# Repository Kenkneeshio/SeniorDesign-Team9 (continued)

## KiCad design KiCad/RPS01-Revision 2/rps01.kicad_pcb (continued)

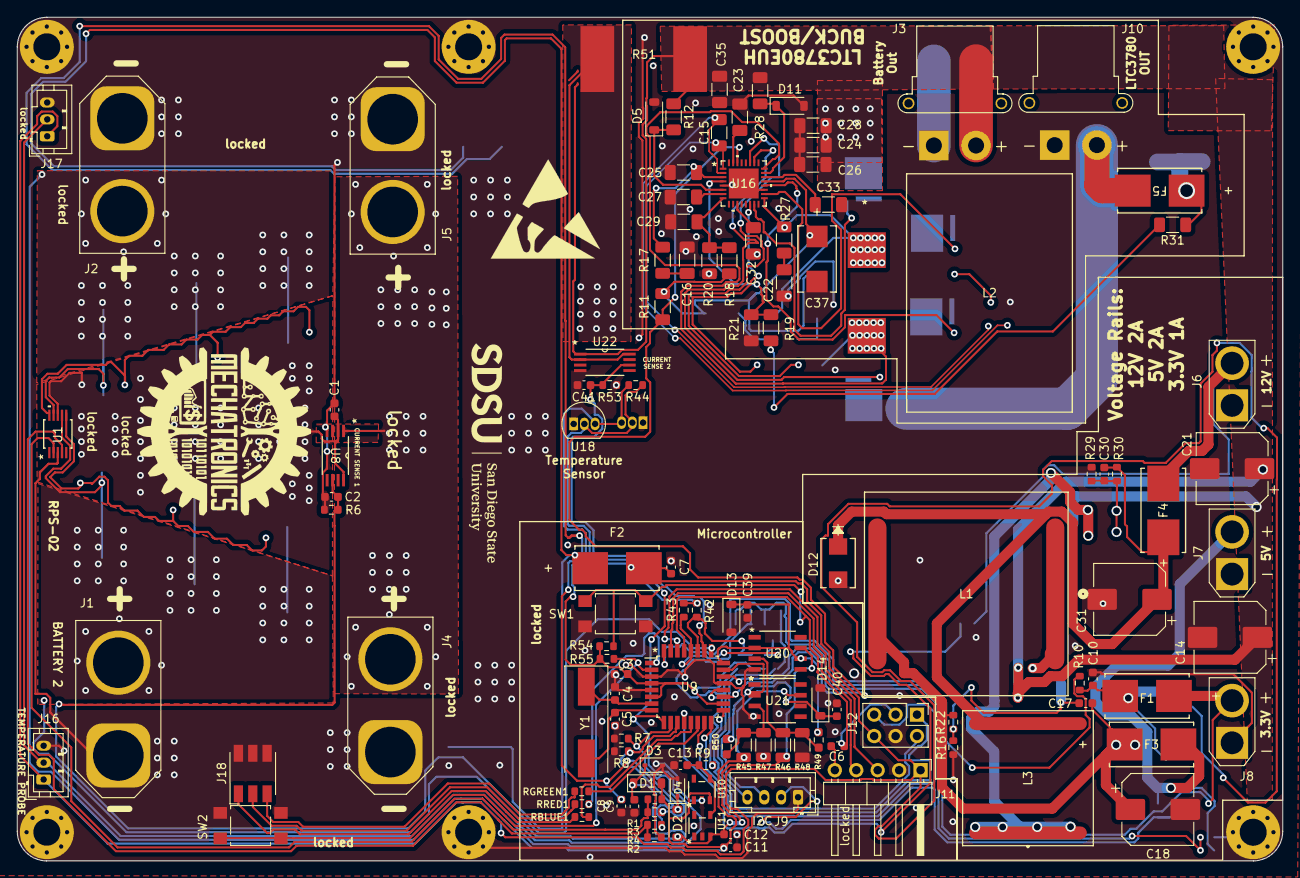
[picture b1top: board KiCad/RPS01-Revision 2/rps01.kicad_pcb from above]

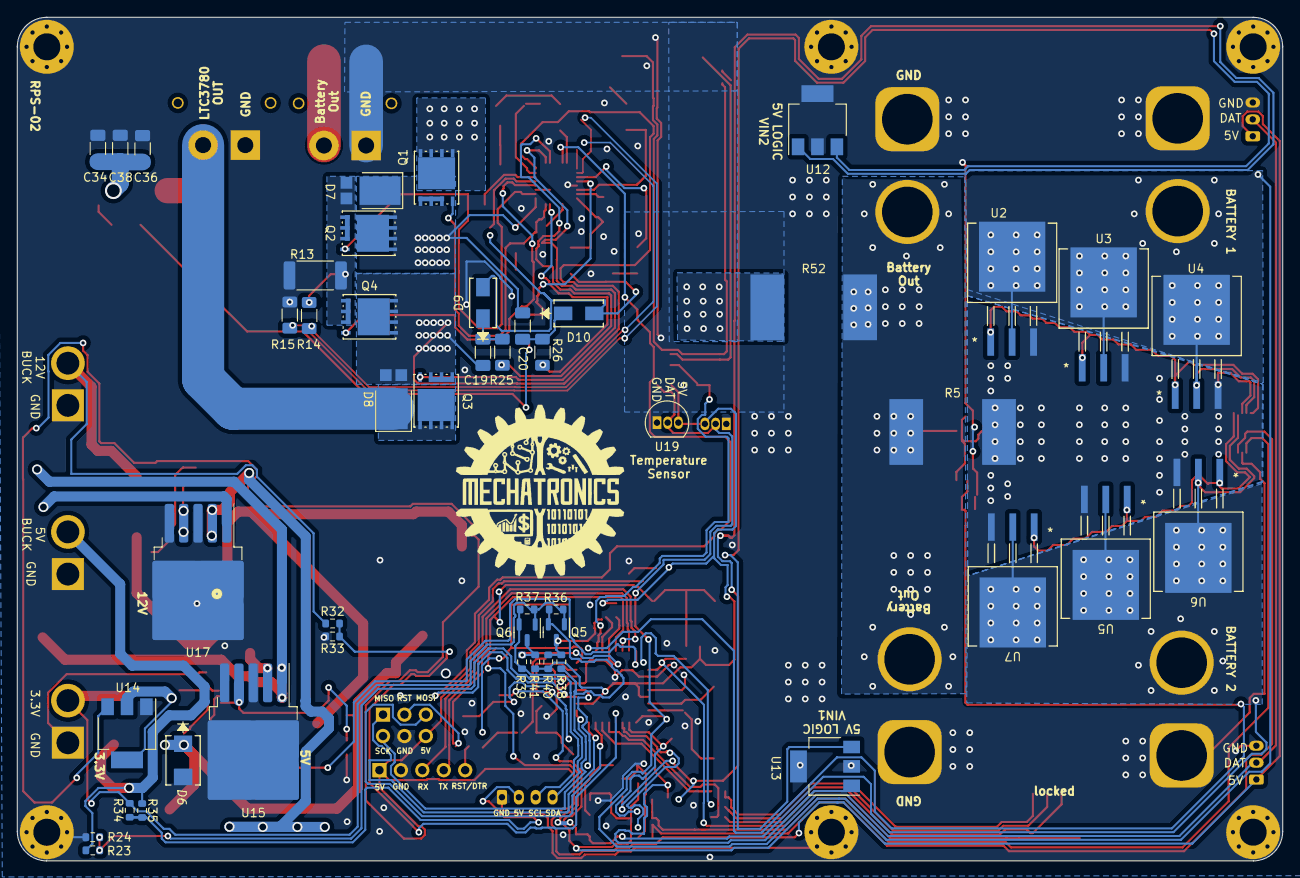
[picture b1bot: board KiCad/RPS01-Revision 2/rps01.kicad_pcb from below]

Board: 2 copper layers, 150.0 x 100.0 mm, 173 parts (47 on the bottom side), 88 nets.

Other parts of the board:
C11, C12, C13: 0.1u; C_0603_1608Metric
R9, R10: 0; R_0603_1608Metric
R51: 3m; CSS2H-5930R
R52: 0; CSS2H-5930R
U10, U11: ADR02AUJZ-REEL7; ADR02AUJZ_REEL7_UJ_5_ADI

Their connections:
+BATT: R51.1, R52.1, R52.2; also elsewhere on the board
+BATT2: R51.2; also elsewhere on the board
AREF: R9.2; also elsewhere on the board
unnamed: C13.1, R9.1, U10.4 (VOUT), U11.4 (VOUT)
PD2: R10.1; also elsewhere on the board

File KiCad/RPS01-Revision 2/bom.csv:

Designator,Footprint,Quantity,Value,LCSC Part #,MFR Part #,Description
"C1, C2, C11, C12, C13, C3, C39, C40, C41",603,9,0.1u,C91183,CC0603JRX7R9BB104,50V 100nF X7R ±5% 0603 Multilayer Ceramic Capacitors MLCC - SMD/SMT ROHS
C10,603,1,22u,C159801,CL10A226MQ8NRNE,6.3V 22uF X5R ±20% 0603 Multilayer Ceramic Capacitors MLCC - SMD/SMT ROHS
C15,1206,1,68p,C440203,GRM31A5C3A680JW01D,1kV 68pF null ±5% 1206 Multilayer Ceramic Capacitors MLCC - SMD/SMT ROHS
C16,1206,1,3.3n,C2847434,FN31N332J500PXG,50V 3.3nF C0G ±5% 1206 Multilayer Ceramic Capacitors MLCC - SMD/SMT ROHS
"C18, C31",CP_Elec_8x10,2,220u,C3008507,EMZA350ARA221MHA0G,"220uF 35V 300mA@120Hz ±20% SMD,D8xL10mm Aluminum Electrolytic Capacitors - SMD ROHS"
C22,1206,1,1n,C541590,CC1206FRNPO9BN102,50V 1nF NP0 ±1% 1206 Multilayer Ceramic Capacitors MLCC - SMD/SMT ROHS
C23,1206,1,.22u,C464977,GRM31C5C1H224JE02L,50V 220nF C0G ±5% 1206 Multilayer Ceramic Capacitors MLCC - SMD/SMT ROHS
"C24, C26, C28",1206,3,10u 35V,C412612,GMJ316BB7106KLHT,35V 10uF X7R ±10% 1206 Multilayer Ceramic Capacitors MLCC - SMD/SMT ROHS
C25,1206,1,47p,C1916,1206CG470J500NT,50V 47pF C0G ±5% 1206 Multilayer Ceramic Capacitors MLCC - SMD/SMT ROHS
C27,1206,1,1000p,C717608,TCC1206X7R102K202FT,2kV 1000pF X7R ±10% 1206 Multilayer Ceramic Capacitors MLCC - SMD/SMT ROHS
C29,1206,1,10000p,C55077,1206B103K101NT,100V 10nF X7R ±10% 1206 Multilayer Ceramic Capacitors MLCC - SMD/SMT ROHS
C32,1206,1,0.01u,C296117,1206N103G500CT,50V 10nF NP0 ±2% 1206 Multilayer Ceramic Capacitors MLCC - SMD/SMT ROHS
C33,1206,1,1u,C85867,GCM31MR71H105KA55L,50V 1uF X7R ±10% 1206 Multilayer Ceramic Capacitors MLCC - SMD/SMT ROHS
"C34, C36, C38",1206,3,22u 16V,C412630,LMK316ABJ226KL-T,10V 22uF X5R ±10% 1206 Multilayer Ceramic Capacitors MLCC - SMD/SMT ROHS
C35,1206,1,0.1u,C97946,GRM31C5C1H104JA01L,50V 100nF C0G ±5% 1206 Multilayer Ceramic Capacitors MLCC - SMD/SMT ROHS
"C4, C5",603,2,22p,C296053,0603N220F101CT,100V 22pF NP0 ±1% 0603 Multilayer Ceramic Capacitors MLCC - SMD/SMT ROHS
C6,603,1,100n,C128615,0603B103J500CT,50V 10nF X7R ±5% 0603 Multilayer Ceramic Capacitors MLCC - SMD/SMT ROHS
"C8, C9",603,2,0.22u,C726561,AC0603KRX7R8BB224,25V 220nF X7R ±10% 0603 Multilayer Ceramic Capacitors MLCC - SMD/SMT ROHS
"D1, D2",D_SOD-123,2,B0540W-7-F,C154764,B0540W-7-F,40V 510mV@500mA 500mA SOD-123 Schottky Barrier Diodes (SBD) ROHS
"D10, D9",SMC(DO-214AB),2,B0540W,C110486,B340-13-F,40V 500mV@3A 3A SMC(DO-214AB) Schottky Barrier Diodes (SBD) ROHS
D11,SOD-123,1,36V Zener,C444414,DDZ36-7,±2.5% Single 35.36V~37.19V 310mW 36V SOD-123 Zener Diodes ROHS
"D12, D6",DO-214AA,2,SSB43L-E3/52T,C5338051,DO-214AA,40V 0.45V 5A DO-214AA Schottky Barrier Diodes (SBD) ROHS
"D13, D14",SOD-123,2,MMSZ5247BT1G,C236089,MMSZ5247BT1G,±5% Single 16.15V~17.85V 500mW 17V SOD-123 Zener Diodes ROHS
"D3, D4",SOD-323,2,MM3Z5V1ST1G,"C236206",MM3Z5V1ST1G,±2% Single 4.98V~5.2V 300mW 5.1V SOD-323 Zener Diodes ROHS
"Q5, Q6",SOT-23(TO-236),2,BSS138,C358381,BSS138,"50V 220mA 3.5Ω@10V,220mA 360mW N Channel SOT-23(TO-236) MOSFETs ROHS"
"R1, R2, R35, R38, R39, R49, R50, R9",603,8,0,C269698,RMC060301%N,100mW 1% 0Ω 0603 Chip Resistor - Surface Mount ROHS
R10,603,1,0,C269698,RMC060301%N,100mW 1% 0Ω 0603 Chip Resistor - Surface Mount ROHS
R11,1206,1,10k,C104595,RTT061002FTP,250mW ±100ppm/℃ ±1% 10kΩ 1206 Chip Resistor - Surface Mount ROHS
R12,1206,1,51K,C319552,AR06DTDV5102,250mW Thin Film Resistor ±0.5% ±50ppm/℃ 51kΩ 1206 Chip Resistor - Surface Mount ROHS
R13,2512,1,25m 1%,C2903480,HoJLR2512-3W-25mR-1%,3W 25mΩ 2512 Current Sense Resistors/Shunt Resistors ROHS
"R14, R15",1206,2,100 1%,C409744,AR06FTCV1000,250mW Thin Film Resistor ±25ppm/℃ ±1% 100Ω 1206 Chip Resistor - Surface Mount ROHS
"R16, R29",603,2,1k,C100050,"RC0603DR-071KL",100mW Thick Film Resistors ±100ppm/℃ ±0.5% 1kΩ 0603 Chip Resistor - Surface Mount ROHS
R17,1206,1,30K,C171081,WR12X3002FTL,250mW Thick Film Resistors ±100ppm/℃ ±1% 30kΩ 1206 Chip Resistor - Surface Mount ROHS
R18,1206,1,47.5K 1%,C319618,AR06BTDV4752,250mW Thin Film Resistor ±50ppm/℃ ±0.1% 47.5kΩ 1206 Chip Resistor - Surface Mount ROHS
R20,1206,1,12.4K 1%,C139133,1206W4F1242T5E,250mW Thick Film Resistors ±100ppm/℃ ±1% 12.4kΩ 1206 Chip Resistor - Surface Mount ROHS
R21,1206,1,8.06K 1%,C323152,RS-06K8061FT,250mW ±100ppm/℃ ±1% 8.06kΩ 1206 Chip Resistor - Surface Mount ROHS
"R25, R26",1206,2,0,C2907363,FRC1206F0000TS,250mW Thick Film Resistors ±1% 0Ω 1206 Chip Resistor - Surface Mount ROHS
R27,1206,1,1,C2960691,FRC1206F1R05TS,250mW Thick Film Resistors ±1% ±200ppm/℃ 1.05Ω 1206 Chip Resistor - Surface Mount ROHS
"R28, R31",1206,2,10,C2933578,FRC1206F10R5TS,250mW Thick Film Resistors ±100ppm/℃ ±1% 10.5Ω 1206 Chip Resistor - Surface Mount ROHS
R30,603,1,"8.87k
",C2998144,FRC0603F8871TS,100mW Thick Film Resistors ±100ppm/℃ ±1% 8.87kΩ 0603 Chip Resistor - Surface Mount ROHS
"R36, R37, R40, R41",603,4,10K,C191124,ERJ3EKF1002V,100mW Thick Film Resistors ±100ppm/℃ ±1% 10000Ω 0603 Chip Resistor - Surface Mount ROHS
"R42, R43, R44, R54, R55, R7, R8",603,7,4.7K,C103656,RTT034701FTP,100mW Thick Film Resistors ±100ppm/℃ ±1% 4.7kΩ 0603 Chip Resistor - Surface Mount ROHS
"R45, R46",1206,2,1.2M,C323198,RS-06L1204FT,250mW ±1% ±250ppm/℃ 1.2MΩ 1206 Chip Resistor - Surface Mount ROHS
"R47, R48",1206,2,510K,C2114457,AA1206FR-07510KL,250mW Thick Film Resistors ±1% ±150ppm/℃ 510kΩ 1206 Chip Resistor - Surface Mount ROHS
R6,603,1,150k,C319876,AR03BTCX1503,100mW Thin Film Resistor ±25ppm/℃ ±0.1% 150kΩ 0603 Chip Resistor - Surface Mount ROHS
RBLUE1,603,1,150 Blue,C3017754,SCR0603J150R,±5% 150Ω 0603 Chip Resistor - Surface Mount ROHS
RGREEN1,603,1,150 Green,C3017754,SCR0603J150R,±5% 150Ω 0603 Chip Resistor - Surface Mount ROHS
RRED1,603,1,100 RED,C2906981,FRC0603F1000TS,100mW Thick Film Resistors ±100ppm/℃ ±1% 100Ω 0603 Chip Resistor - Surface Mount ROHS
SW1,SW_SPST_TL3305A,1,RST,C2886899,TL3305AF160QG,NO 50mA 100MΩ 500000 Times 12V 160gf Brick nogging SPST - Tactile Switches ROHS
SW2,SW_SPST_TL3305A,1,Display Button,C2886899,TL3305AF160QG,NO 50mA 100MΩ 500000 Times 12V 160gf Brick nogging SPST - Tactile Switches ROHS
"U10, U11",TSOT-5L,2,ADR02AUJZ-REEL7,C141936,ADR02AUJZ-REEL7,5V ±0.1% 7V~36V 10mA Fixed SOT-23-5 Voltage References ROHS
"U12, U13",SOT-223-4,2,LM340MPX-5.0/NOPB,C2860024,LM340MPX-5.0/NOPB,70dB@(120Hz) 1.5A null 5V positive 35V SOT-223-4 Linear Voltage Regulators (LDO) ROHS
"U20, U21",SOP-8,2,UA741CDT,C7111,UA741CDT,10nA 1 1MHz SOP-8 Operational Amplifier ROHS

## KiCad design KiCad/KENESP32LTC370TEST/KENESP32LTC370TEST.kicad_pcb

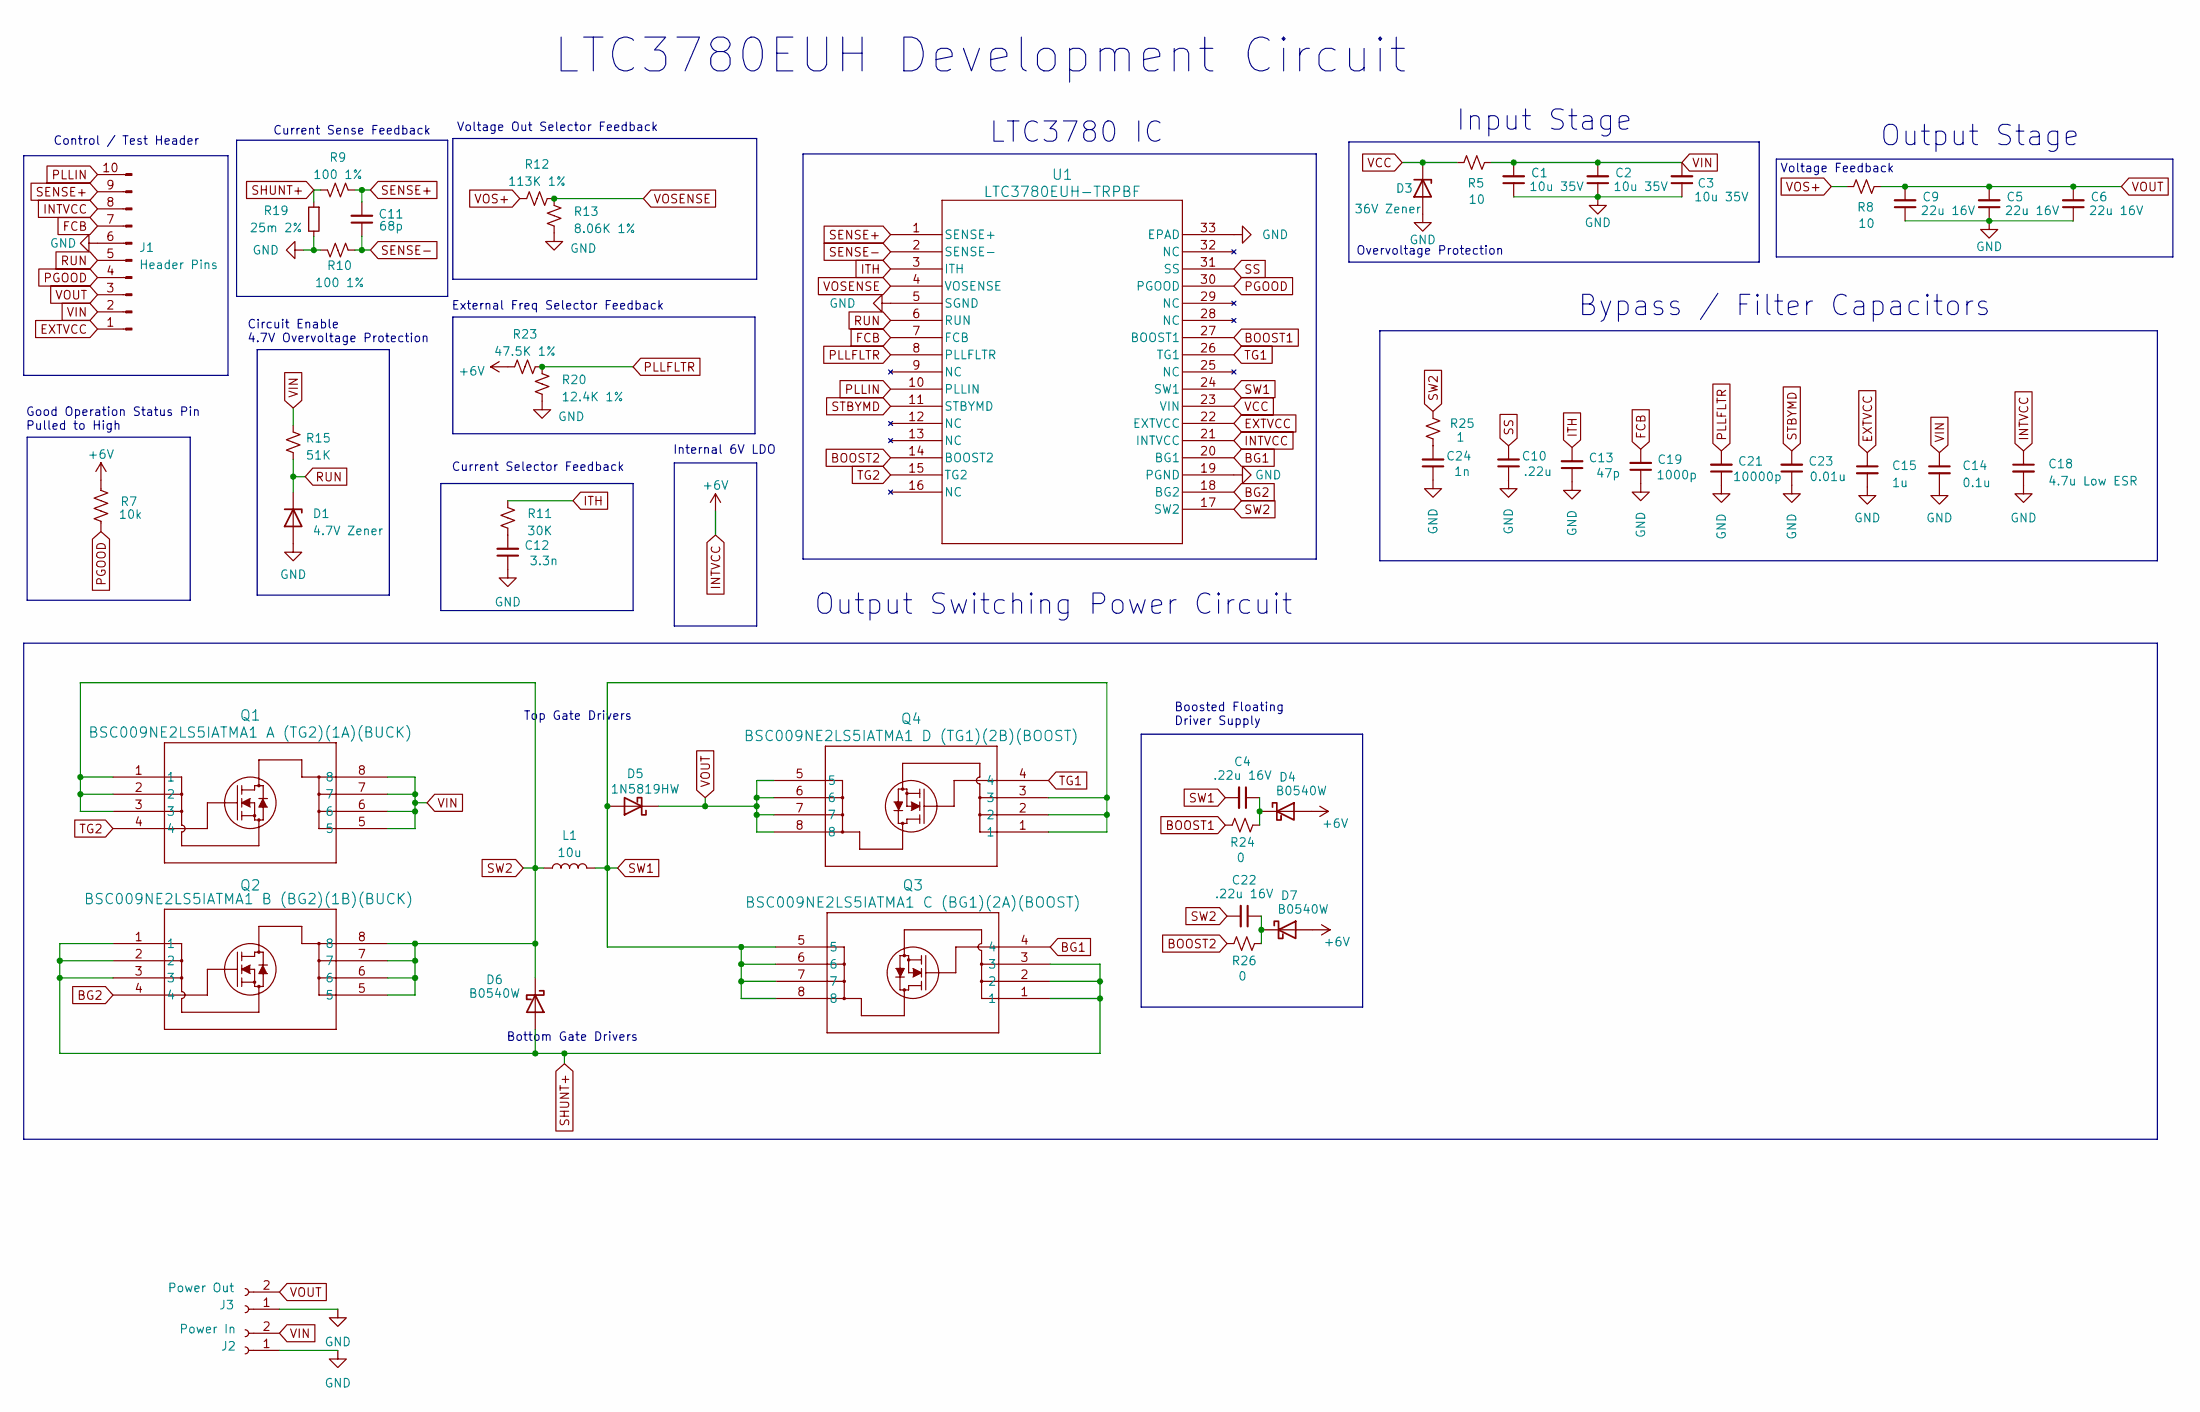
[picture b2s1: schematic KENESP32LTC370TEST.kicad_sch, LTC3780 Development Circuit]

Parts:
C1, C2, C3: 10u 35V; C_1206_3216Metric_Pad1.33x1.80mm_HandSolder
C4, C22: .22u 16V; C_1206_3216Metric_Pad1.33x1.80mm_HandSolder
C5, C6, C9: 22u 16V; C_1206_3216Metric_Pad1.33x1.80mm_HandSolder
C10: .22u; C_1206_3216Metric_Pad1.33x1.80mm_HandSolder
C11: 68p; C_1206_3216Metric_Pad1.33x1.80mm_HandSolder
C12: 3.3n; C_1206_3216Metric_Pad1.33x1.80mm_HandSolder
C13: 47p; C_1206_3216Metric_Pad1.33x1.80mm_HandSolder
C14: 0.1u; C_1206_3216Metric_Pad1.33x1.80mm_HandSolder
C15: 1u; C_1206_3216Metric_Pad1.33x1.80mm_HandSolder
C18: 4.7u Low ESR; LOWESRCAPMP7.6X4.3_3.1N_KEM
C19: 1000p; C_1206_3216Metric_Pad1.33x1.80mm_HandSolder
C21: 10000p; C_1206_3216Metric_Pad1.33x1.80mm_HandSolder
C23: 0.01u; C_1206_3216Metric_Pad1.33x1.80mm_HandSolder
C24: 1n; C_1206_3216Metric_Pad1.33x1.80mm_HandSolder
D1: 4.7V Zener; D_SOD-123
D3: 36V Zener; D_SOD-123
D4, D6, D7: B0540W; CR_SMA_320-340AE_DIO
D5: 1N5819HW; CR_SMA_320-340AE_DIO
J1: Header Pins; PinHeader_1x10_P2.54mm_Vertical
J2: Power In; AMASS_XT30U-M_1x02_P5.0mm_Vertical
J3: Power Out; AMASS_XT30U-F_1x02_P5.0mm_Vertical
L1: 10u; IND_410680_WRE
Q1: BSC009NE2LS5IATMA1 A (TG2)(1A)(BUCK); PG-TDSON-8_INF
Q2: BSC009NE2LS5IATMA1 B (BG2)(1B)(BUCK); PG-TDSON-8_INF
Q3: BSC009NE2LS5IATMA1 C (BG1)(2A)(BOOST); PG-TDSON-8_INF
Q4: BSC009NE2LS5IATMA1 D (TG1)(2B)(BOOST); PG-TDSON-8_INF
R5, R8: 10; R_1206_3216Metric_Pad1.30x1.75mm_HandSolder
R7: 10k; R_1206_3216Metric_Pad1.30x1.75mm_HandSolder
R9, R10: 100 1%; R_1206_3216Metric_Pad1.30x1.75mm_HandSolder
R11: 30K; R_1206_3216Metric_Pad1.30x1.75mm_HandSolder
R12: 113K 1%; R_1206_3216Metric_Pad1.30x1.75mm_HandSolder
R13: 8.06K 1%; R_1206_3216Metric_Pad1.30x1.75mm_HandSolder
R15: 51K; R_1206_3216Metric_Pad1.30x1.75mm_HandSolder
R19: 25m 2%; R_1206_3216Metric_Pad1.30x1.75mm_HandSolder
R20: 12.4K 1%; R_1206_3216Metric_Pad1.30x1.75mm_HandSolder
R23: 47.5K 1%; R_1206_3216Metric_Pad1.30x1.75mm_HandSolder
R24, R26: 0; R_1206_3216Metric_Pad1.30x1.75mm_HandSolder
R25: 1; R_1206_3216Metric_Pad1.30x1.75mm_HandSolder
U1: LTC3780EUH-TRPBF; QFN-32_UH_LIT

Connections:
BG1: Q3.4, U1.20 (BG1)
BG2: Q2.4, U1.18 (BG2)
BOOST1: R24.1, U1.27 (BOOST1)
BOOST2: R26.1, U1.14 (BOOST2)
EXTVCC: C15.1, J1.1, U1.22 (EXTVCC)
FCB: C19.2, J1.7, U1.7 (FCB)
GND: C1.1, C2.1, C3.1, C5.1, C6.1, C9.1, C10.1, C12.1, C13.1, C14.2, C15.2, C18.2, C19.1, C21.1, C23.1, C24.1, D1.2 (A), D3.2 (A), J1.6, J2.1, J3.1, R10.2, R13.2, R19.2, R20.2, U1.5 (SGND), U1.19 (PGND), U1.33 (EPAD)
INTVCC: C18.1, D4.2 (A), D7.2 (A), J1.8, R7.1, R23.1, U1.21 (INTVCC)
ITH: C13.2, R11.1, U1.3 (ITH)
unnamed: C12.2, R11.2
unnamed: C24.2, R25.1
unnamed: C4.1, D4.1 (K), R24.2
unnamed: C22.1, D7.1 (K), R26.2
PGOOD: J1.4, R7.2, U1.30 (PGOOD)
PLLFLTR: C21.2, R20.1, R23.2, U1.8 (PLLFLTR)
PLLIN: J1.10, U1.10 (PLLIN)
RUN: D1.1 (K), J1.5, R15.2, U1.6 (RUN)
SENSE+: C11.2, J1.9, R9.1, U1.1 (SENSE+)
SENSE-: C11.1, R10.1, U1.2 (SENSE-)
SHUNT+: D6.2 (A), Q2.1, Q2.2, Q2.3, Q3.1, Q3.2, Q3.3, R9.2, R19.1
SS: C10.2, U1.31 (SS)
STBYMD: C23.2, U1.11 (STBYMD)
SW1: C4.2, D5.2 (A), L1.2, Q3.5, Q3.6, Q3.7, Q3.8, Q4.1, Q4.2, Q4.3, U1.24 (SW1)
SW2: C22.2, D6.1 (K), L1.1, Q1.1, Q1.2, Q1.3, Q2.5, Q2.6, Q2.7, Q2.8, R25.2, U1.17 (SW2)
TG1: Q4.4, U1.26 (TG1)
TG2: Q1.4, U1.15 (TG2)
VCC: D3.1 (K), R5.2, U1.23 (VIN)
VIN: C1.2, C2.2, C3.2, C14.1, J1.2, J2.2, Q1.5, Q1.6, Q1.7, Q1.8, R5.1, R15.1
VOS+: R8.2, R12.1
VOSENSE: R12.2, R13.1, U1.4 (VOSENSE)
VOUT: C5.2, C6.2, C9.2, D5.1 (K), J1.3, J3.2, Q4.5, Q4.6, Q4.7, Q4.8, R8.1

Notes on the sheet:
Control / Test Header
Boosted Floating Driver Supply
LTC3780 IC
Input Stage
Voltage Out Selector Feedback
Top Gate Drivers
LTC3780EUH Development Circuit
Bypass / Filter Capacitors
External Freq Selector Feedback
Good Operation Status Pin Pulled to High
Overvoltage Protection
Internal 6V LDO
Circuit Enable 4.7V Overvoltage Protection
Voltage Feedback
Current Selector Feedback
Output Switching Power Circuit
Bottom Gate Drivers
Current Sense Feedback
Output Stage

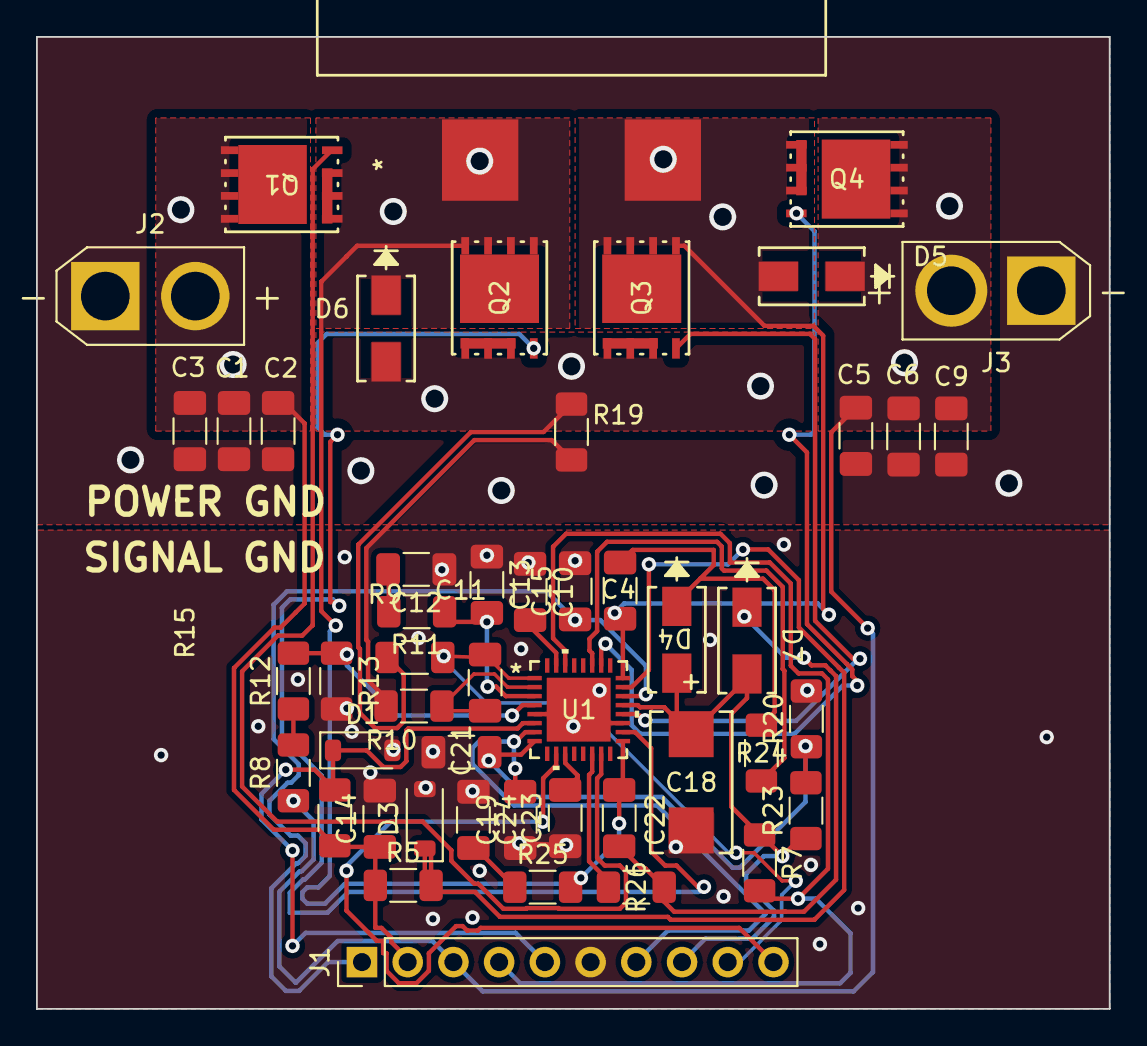
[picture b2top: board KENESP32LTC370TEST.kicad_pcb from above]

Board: 2 copper layers, 59.6 x 54.0 mm, 49 parts (0 on the bottom side), 31 nets.

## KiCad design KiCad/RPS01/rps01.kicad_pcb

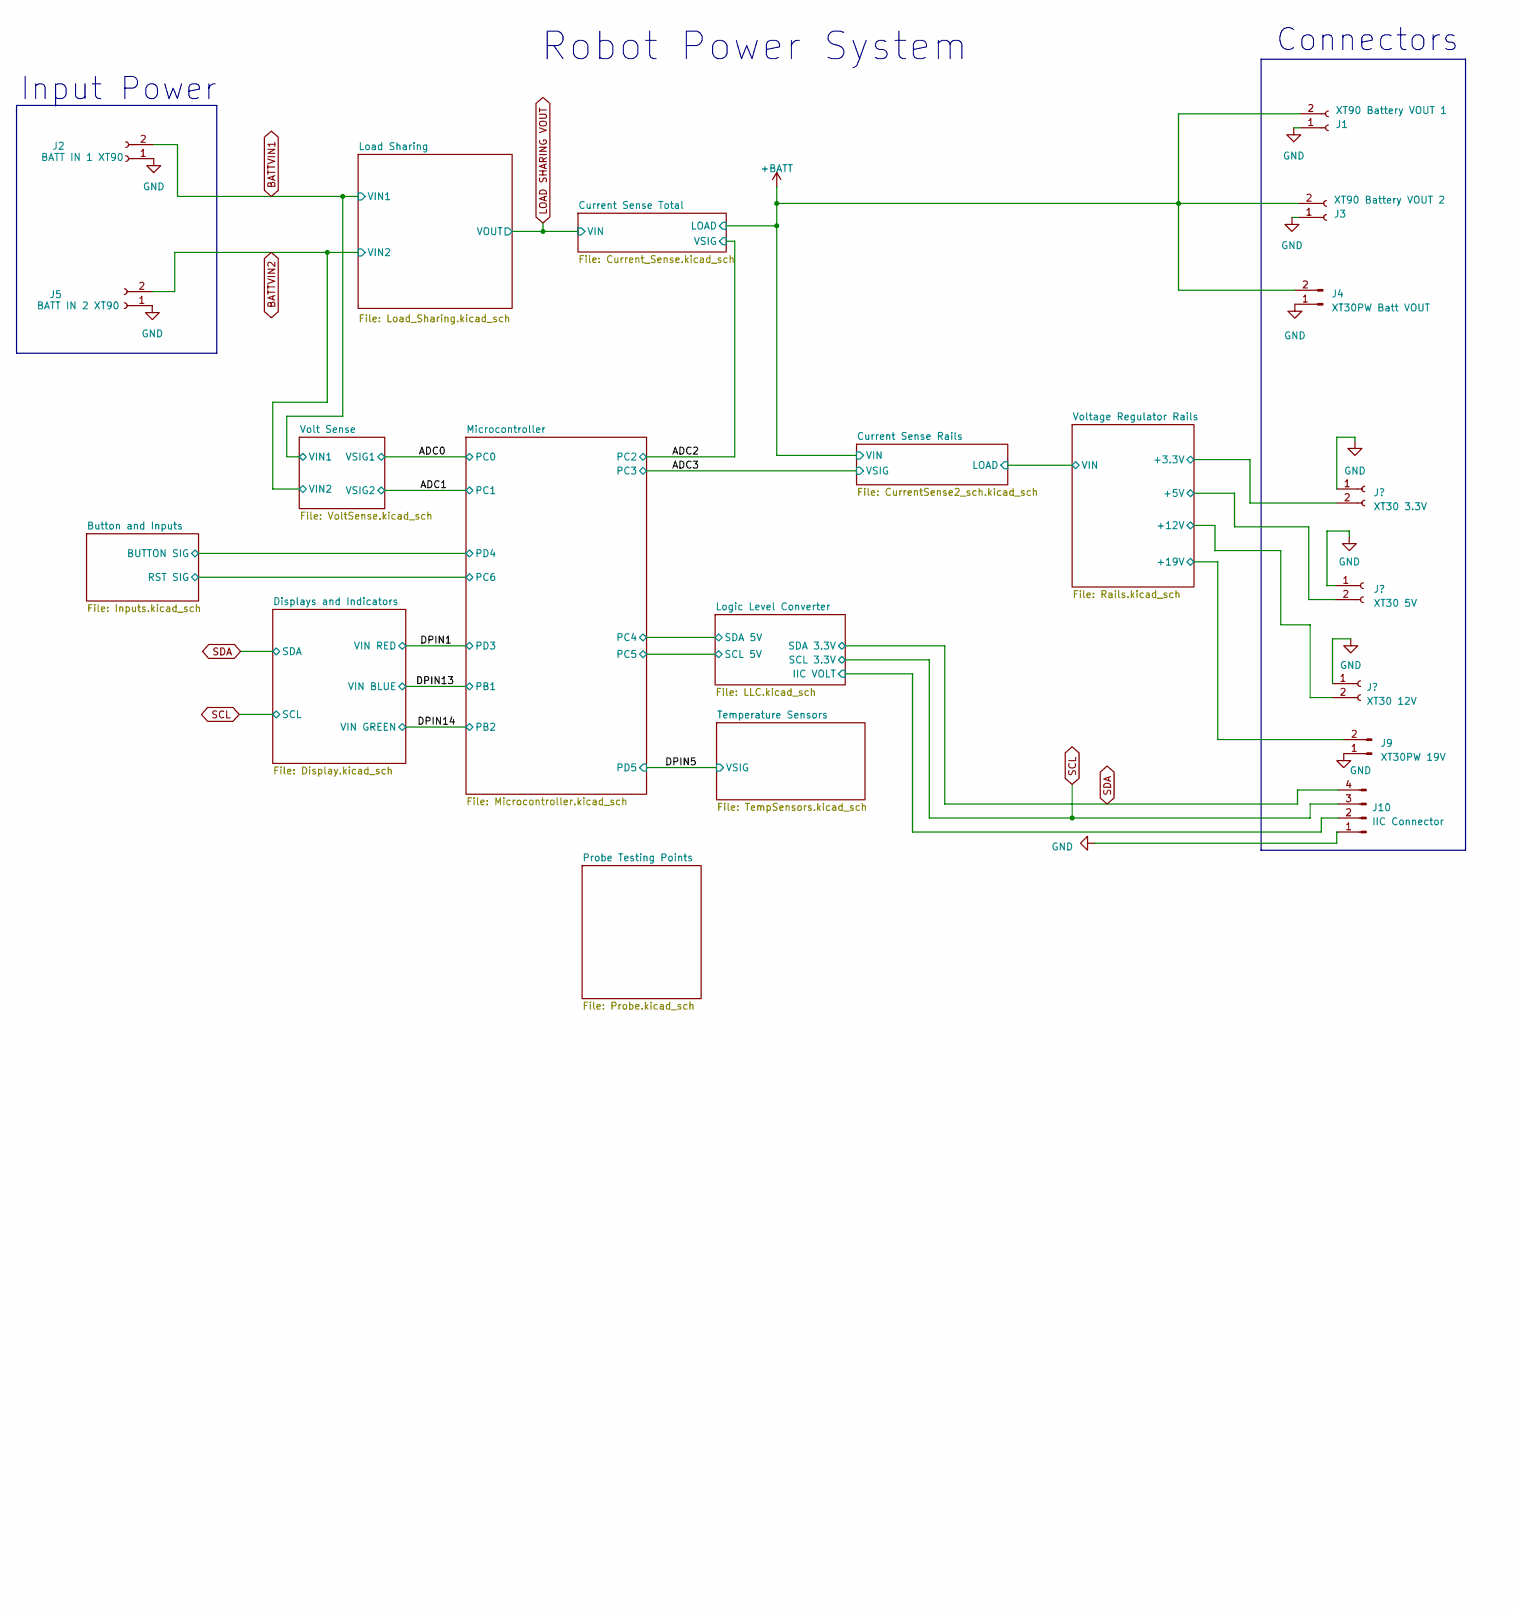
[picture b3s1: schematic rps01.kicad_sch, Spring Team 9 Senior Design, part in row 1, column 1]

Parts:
J1: XT90 Battery VOUT 1; AMASS_XT90-F_1x02_P11.00mm_Vertical
J2: BATT IN 1 XT90; AMASS_XT90-M_1x02_P11.00mm_Vertical
J3: XT90 Battery VOUT 2; AMASS_XT90-F_1x02_P11.00mm_Vertical
J4: XT30PW Batt VOUT; AMASS_XT30PW-F_1x02_P2.50mm_Horizontal
J5: BATT IN 2 XT90; AMASS_XT90-M_1x02_P11.00mm_Vertical
J6: XT30 3.3V; AMASS_XT30U-F_1x02_P5.0mm_Vertical
J7: XT30 5V; AMASS_XT30U-F_1x02_P5.0mm_Vertical
J8: XT30 12V; AMASS_XT30U-F_1x02_P5.0mm_Vertical
J9: XT30PW 19V; AMASS_XT30PW-F_1x02_P2.50mm_Horizontal
J10: IIC Connector; JST_PH_B4B-PH-K_1x04_P2.00mm_Vertical

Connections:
+3.3V: J6.2; also elsewhere on the board
+5V: J7.2; also elsewhere on the board
+12V: J8.2; also elsewhere on the board
+19V: J9.2; also elsewhere on the board
/Logic Level Converter/IIC VOLT: J10.2; also elsewhere on the board
BATTVIN1: J2.2; also elsewhere on the board
BATTVIN2: J5.2; also elsewhere on the board
SCL: J10.3; also elsewhere on the board
SDA: J10.4; also elsewhere on the board

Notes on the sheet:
Connectors
Robot Power System
Input Power

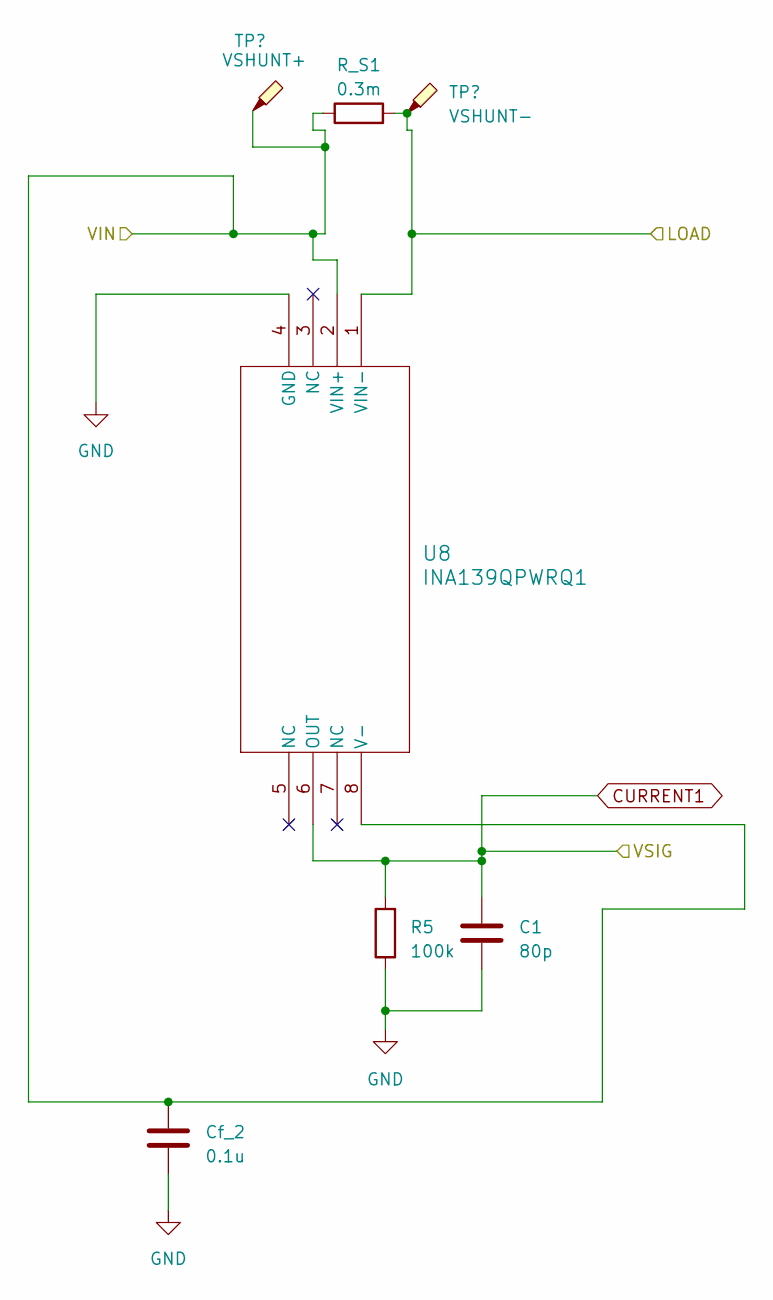
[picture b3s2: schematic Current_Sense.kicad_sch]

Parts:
C1: 80p; C_0603_1608Metric
Cf_2: 0.1u; C_0603_1608Metric
R5: 100k; R_0603_1608Metric
R_S1: 0.3m; CSS2H-5930R
TP1: VSHUNT-; CONN1_RCU-0C_TEC
TP2: VSHUNT+; CONN1_RCU-0C_TEC
U8: INA139QPWRQ1; INA139_PW8

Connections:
CURRENT1: C1.1, R5.2, U8.6 (OUT); also elsewhere on the board

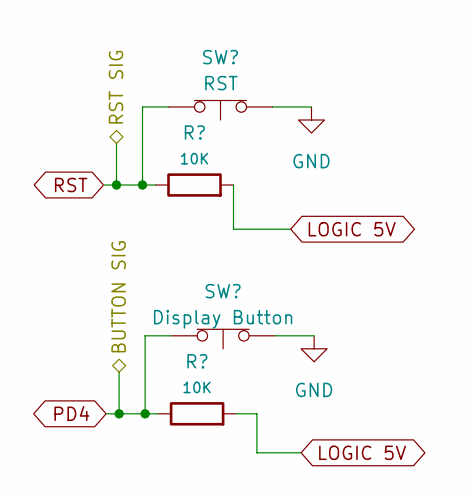
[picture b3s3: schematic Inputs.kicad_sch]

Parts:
R32, R33: 10K; R_0603_1608Metric
SW1: RST; SW_SPST_PTS645
SW2: Display Button; SW_SPST_PTS645

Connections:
PD4: R33.1, SW2.2 (B); also elsewhere on the board
RST: R32.1, SW1.2 (B); also elsewhere on the board

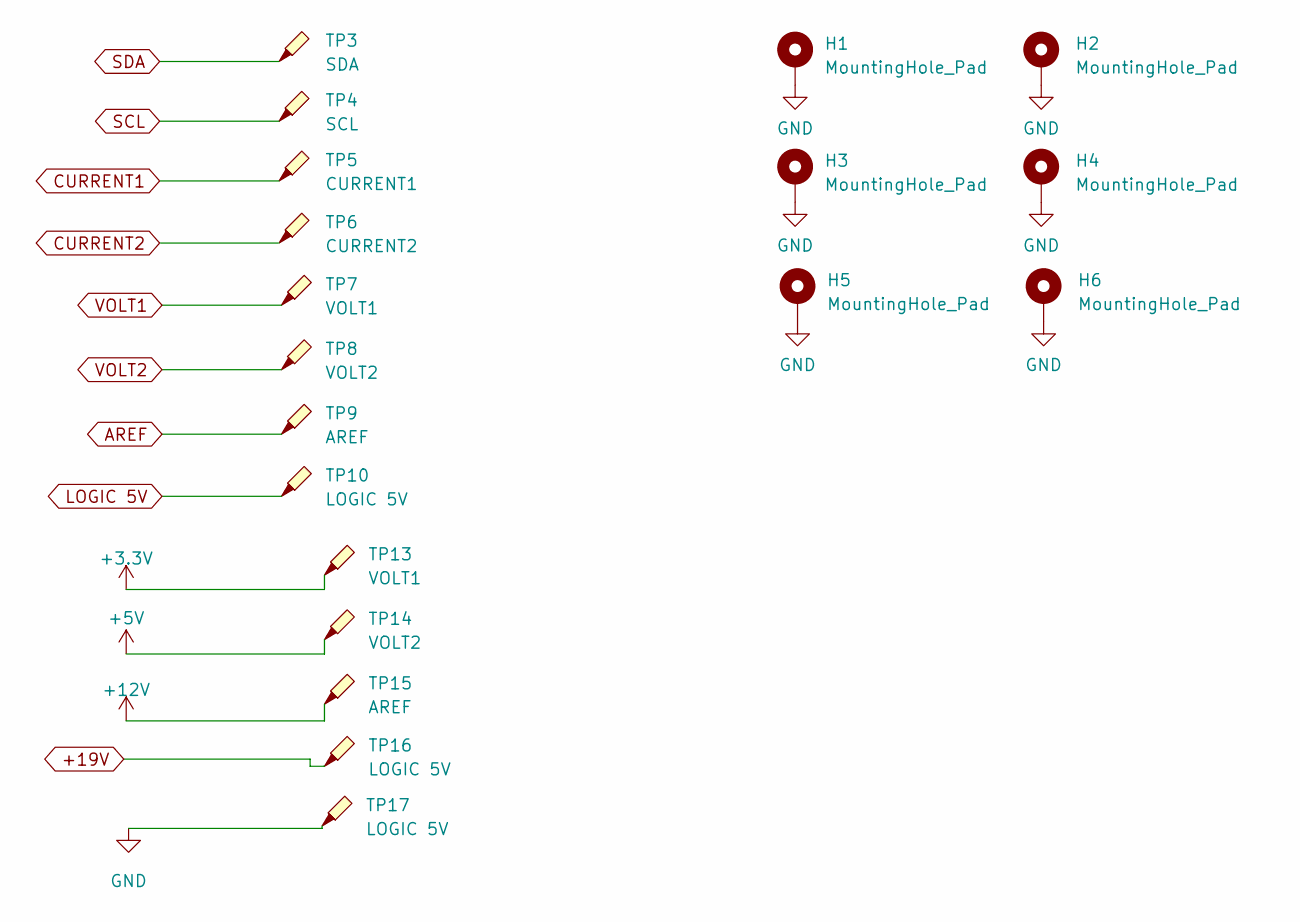
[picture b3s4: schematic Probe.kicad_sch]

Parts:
H1, H2, H3, H4, H5, H6: MountingHole_Pad; MountingHole_3.2mm_M3_Pad_Via
TP3: SDA; CONN1_RCU-0C_TEC
TP4: SCL; CONN1_RCU-0C_TEC
TP5: CURRENT1; CONN1_RCU-0C_TEC
TP6: CURRENT2; CONN1_RCU-0C_TEC
TP7, TP13: VOLT1; CONN1_RCU-0C_TEC
TP8, TP14: VOLT2; CONN1_RCU-0C_TEC
TP9, TP15: AREF; CONN1_RCU-0C_TEC
TP10, TP16, TP17: LOGIC 5V; CONN1_RCU-0C_TEC

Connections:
+3.3V: TP13.1; also elsewhere on the board
+5V: TP14.1; also elsewhere on the board
+12V: TP15.1; also elsewhere on the board
+19V: TP16.1; also elsewhere on the board
AREF: TP9.1; also elsewhere on the board
CURRENT1: TP5.1; also elsewhere on the board
CURRENT2: TP6.1; also elsewhere on the board
SCL: TP4.1; also elsewhere on the board
SDA: TP3.1; also elsewhere on the board
VOLT1: TP7.1; also elsewhere on the board
VOLT2: TP8.1; also elsewhere on the board

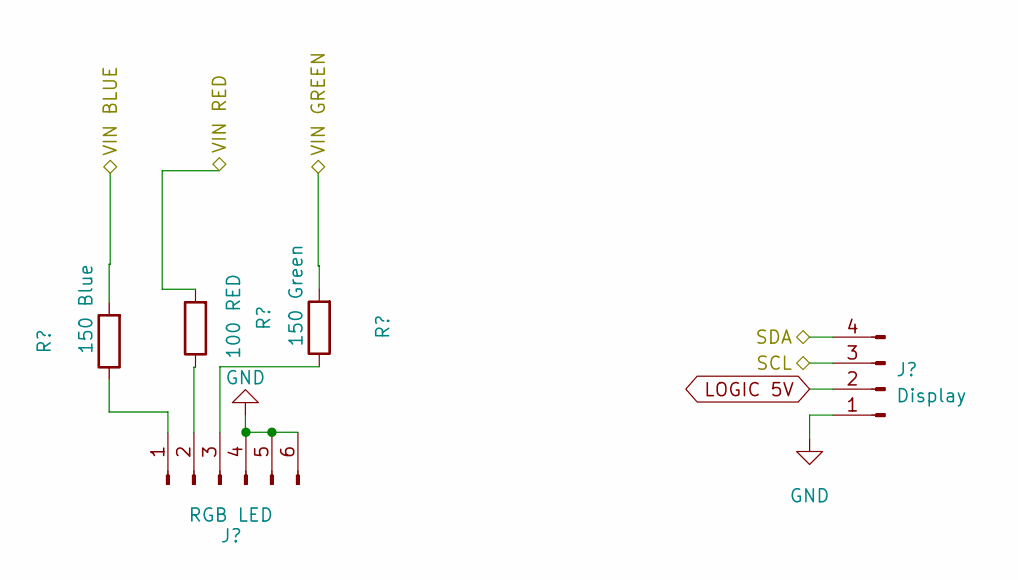
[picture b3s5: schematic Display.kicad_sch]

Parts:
J14: RGB LED; LED_RGB_5050-6
J15: Display; 128x64OLED
R29: 150 Blue; R_0603_1608Metric
R30: 100 RED; R_0603_1608Metric
R31: 150 Green; R_0603_1608Metric

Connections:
/DPIN1: R29.2; also elsewhere on the board
/DPIN13: R30.2; also elsewhere on the board
CURRENT2: R31.2; also elsewhere on the board
SCL: J15.3; also elsewhere on the board
SDA: J15.4; also elsewhere on the board
